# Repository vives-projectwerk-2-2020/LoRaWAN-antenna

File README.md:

# The LoRaWAN-antenna board

This is the explanation of how the antenna PCB board came. And how you can make one yourself.
This PCB described here must then be connected to the main PCB. Below you can see what it looks like.

This Antenna on the board is based on [this](http://www.ti.com/lit/an/swra228c/swra228c.pdf) design.

## Explanation of the Antenna PCB board

Below you see the antenna board. The PCB antenna on this board is suitable for a frequency around 868MHz.

The antenna will work most efficiently if it is resonant. When it is resonant, the maximum power will be radiated by the antenna. If an antenna is not resonant, some of the power will not be transmitted. The power is reflected back to the transmitter (in our case the RF96 module).

Because of the reflection you have a RF power loss and you could damage the RF96 module and also reduce your transmission range.

You can solve this by doing 2 things:

* Adjust the length of the antenna and,
* add a matching network.

This is discussed below here.

### Adjust length

You can adjust the length here, by scratching away some copper at the end of the antenna. The total length of the last piece of the antenna is 1,25 cm (measured from the outer corner). See the image below for clarification.

By adjusting the length of the antenna, the antenna is now al more suitable for 868MHz.

### Matching network

By adding a matching network now, we can improve the impedance of the antenna more.

The network for adjusting the impedance is a PI network. Below you can see the schematic of the network. The left side of the math unit is connected to the RF96 (the antenna output = pin 9). The right side of the unit is connected to the antenna.

You can observe the matching network below. This consists of 2 capacitors and 1 coil. The values of the capacitors are 2,2pF. The value of the coil is 12nH.

Due to mismatches in impedance, some of the signal is reflected. The ratio of the input to the reflected signal is called the Voltage Standing Wave Ratio (VSWR). This ratio can also be measured in dB, and expressed as Return Loss.

Below you can see that the VSWR at 868MHz is 1.112. This mean that you're return lose is 25.510dB. This is very good, because now less than 1% of the power goes back to the module. This means that more than 99% of the power is used for the communication.

The dimensions of the PCB are also very important. If the dimensions are different from here, you must again determine the length and the matching network.

### RF96

The RF96 module is a module suitable for ultra-long range spread spectrum communications. This module has a 20 dBm power amplifier. This means that you have an output power of 100mW. Because the impedance is now correct, all power will also be radiated effectively.

Below you see the RF95 module. All pins are brought out through the pins. Except the pin that goes to the antenna.
This PCB is then clicked on the main PCB.

### schematic and print in Eagle

Here you can see the schematic drawn in Eagle. At the top you see the pins, these are then connected to the main PCB. below that you see the RF96 chip.
In the middle you see the matching network, which ensures a correct impedance.
The square block on the right is the symbol for your antenna. It is a symbol whose foodprint is the shape of the antenna.

Below you can see what the PCB looks like in eagle.

### tests that happened

You can view the tests that happened in the folder "testing".

## Make it yourself

### Develop the PCB

First you need to develop the PCB. You can do this by sending a zip to a manufacturer. Like for example with this manufacturer([JLCPCB](https://jlcpcb.com/)).
The ZIP file is located here in the root and is called 'LoRaWAN_antenna.zip'. You can download and upload this on the manufacturer's website. If you want to make changes to the PCB you can edit it in the folder 'PCB-antenna-eagle'.

### Order the components

Then you have to order the components. These are the components:

* [coil (12nH)](https://be.farnell.com/te-connectivity/36502a12njtdg/inductor-12n-5-0805-case/dp/1265504?st=)
* [capacitors (2.2pF)](https://be.farnell.com/vishay/vj0805a2r2bxapw1bc/cap-2-2pf-50v-c0g-np0-0805/dp/2896503?st=)
* [RF96 module](https://www.digikey.be/product-detail/en/seeed-technology-co.,-ltd/109990166/1597-1488-ND/7033232?utm_adgroup=RF%20Transceiver%20Modules&utm_source=google&utm_medium=cpc&utm_campaign=Shopping_Product_RF%2FIF%20and%20RFID&utm_term=&productid=7033232&gclid=CjwKCAjwqpP2BRBTEiwAfpiD-0hUd9VhSiN13Y9OhOWbJ38YxABk0f2ujbqdI1xJR1xy0auqC77hRBoC65kQAvD_BwE)
* [male pins](https://be.farnell.com/harwin/m20-9990846/connector-header-tht-2-54mm-8way/dp/1022257)

for 1 PCB you need 2 capacitors, 1 coil, 1 RF95 module and 15 male pins.

### Solder everything together

If you then have your PCB and components, you can start soldering.
You should not scratch the antenna anymore, I have already adjusted this in the last version.
For soldering it is best to start with the RF96 module and then the capacitors and the coil.
Then solder the pins on the last.

## Placing the installation

If you have connected all the boards(main + solar + antenna), you can place this where you want.
There are some things to keep in mind:

* Place the installation in a place where connections can be made to a gateway. On [this](https://www.thethingsnetwork.org/map) map you can see where there is a gateway. If you want a map where you can see the range, it is best to use [this map](https://ttnmapper.org/).

* Place the installation as high as possible. The higher, the fewer obstacles in the way and the greater the chance of connecting to a gateway.

* Do not place the antenna under the solar panels or next to the solar panels. Because this will ensure that a lot of your range is gone.

* The box you use should not be made of metal or a substance containing metal. [This](http://www.farnell.com/datasheets/2360495.pdf?_ga=2.70667346.396449874.1589637555-1552518953.1588835899&_gac=1.258009592.1589039175.CjwKCAjwqdn1BRBREiwAEbZcR9CB4ETaMQ7lKFncoM-7RMHN5OMiYtTP339AnwNVqZjWkSkDVfl0shoCSGMQAvD_BwE) box is ideal. The material from which the box is made is Polycarbonate. This does not contain metal.

* The box with should be placed freely, not against a wall. Also make sure you are at a certain height.

* Make sure the box is not completely closed. It is best to make 1 or 2 small holes at the bottom so that moisture can escape if condensation forms.

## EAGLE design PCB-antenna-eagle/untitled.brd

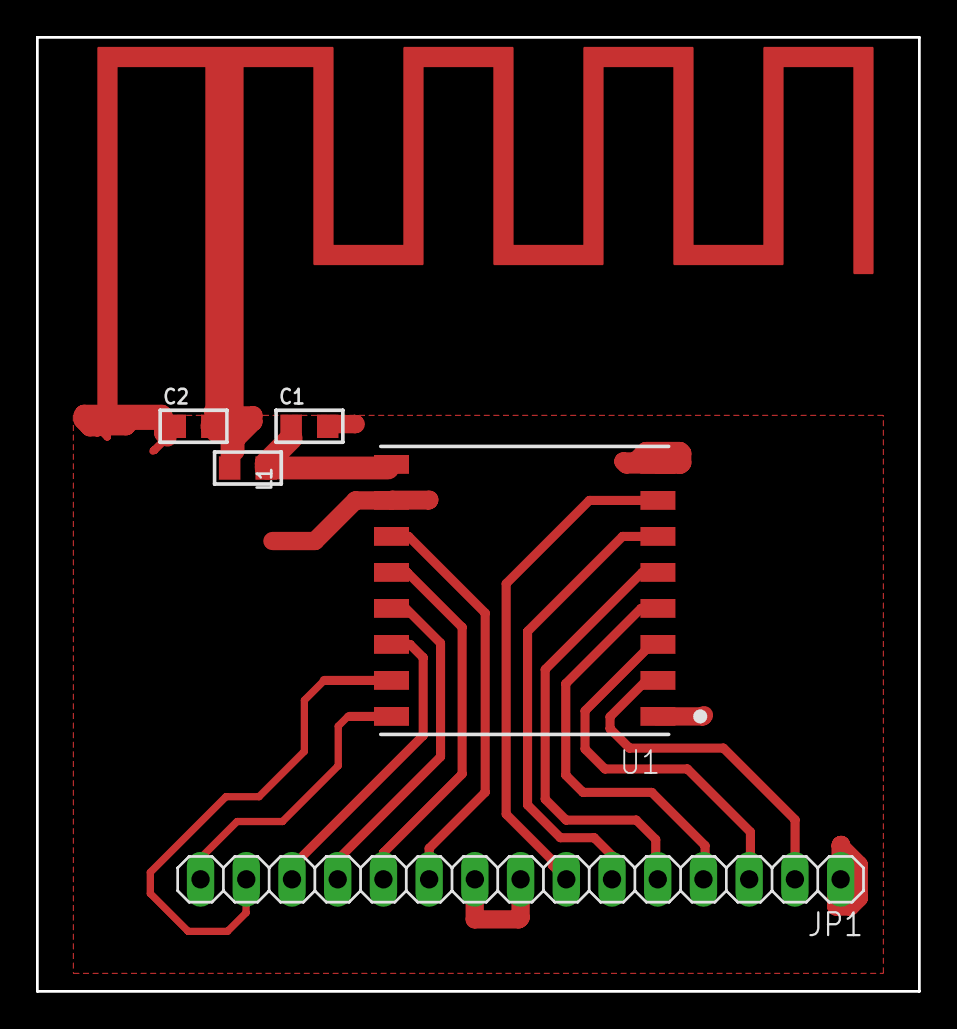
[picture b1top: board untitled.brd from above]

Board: 2 copper layers, 49.0 x 53.0 mm, 6 parts (0 on the bottom side), 15 nets.

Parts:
C1, C2: C0805
JP1: 1X15
L1: L_0805; L0805
U1: RFM95W-868S2; XCVR_RFM95W-868S2
U$1: 868

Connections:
GND: C1.2, C2.1, JP1.1, JP1.8, JP1.9, U1.1, U1.8, U1.10, U$1.P$1
unnamed: C2.2, L1.2, U$1.P$2
unnamed: C1.1, L1.1, U1.9
unnamed: JP1.2, U1.2
unnamed: JP1.3, U1.3
unnamed: JP1.4, U1.4
unnamed: JP1.5, U1.5
unnamed: JP1.6, U1.6
unnamed: JP1.7, U1.7
unnamed: JP1.10, U1.11
unnamed: JP1.11, U1.12
unnamed: JP1.12, U1.13
unnamed: JP1.13, U1.14
unnamed: JP1.14, U1.15
unnamed: JP1.15, U1.16

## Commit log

2020-02-18 add photo of the bests antennas
2020-02-18 research update
2020-02-18 research update 2
2020-02-18 research update 3
2020-02-18 research update 4
2020-02-18 add doc+ research
2020-02-18 PCB-antenna is not optimal
2020-02-19 chanches to word
2020-02-19 Research part 6
2020-02-27 gasket antenna will be to big
2020-02-27 update from research
2020-02-27 found the antenna
2020-02-27 verdere stappen
2020-03-01 design PCB antenna
2020-03-03 add inkcape design from antenna
2020-03-03 add picture of antenna_drawing
2020-03-08 draw the PCB for a part
2020-03-10 groundplane
2020-03-10 add antenna
2020-03-10 full_print
2020-03-10 try to print on mika -- failed
2020-03-11 add pdf for etsing
2020-03-11 add zip for making pcb
2020-03-15 add partlist for prototype
2020-03-15 add some documentation
2020-03-29 solder and test antenna
2020-04-06 solder the board with module
2020-04-11 connect the arduino and RF95 for testing
2020-04-11 level converters
2020-04-14 try to test program
2020-04-21 test the board with the board of Niels - Succcesful
2020-04-21 test the range a bit
2020-04-27 test with better antenna on the gateway
2020-05-04 change PCB antenna to the best dimensions
2020-05-08 different between the two antenna's
2020-05-09 remove some typos
2020-05-09 add matching explanation
2020-05-09 change image
2020-05-09 change name
2020-05-09 add somme explanation about VSWR
2020-05-09 RF95
2020-05-09 add eagle stuff
2020-05-09 add image
2020-05-09 remove some old stuff
2020-05-09 add source and intro
2020-05-09 remove typo
2020-05-09 change
2020-05-09 add upercase letters
2020-05-09 add schematic
2020-05-09 replace PCB
2020-05-09 add components
2020-05-09 add some intro on RF95
2020-05-09 remove some stuff
2020-05-09 replace stuff
2020-05-09 change name folder
2020-05-09 add section testing
2020-05-09 change testing readme
2020-05-09 change documentation about testing
2020-05-09 add some subtitles
2020-05-09 change titles
2020-05-11 add some old stuff
2020-05-11 read and adjust some text
2020-05-11 change text
2020-05-11 retyp some text
2020-05-16 add instalation instrucions
2020-05-20 change RF95 to RF96
2020-05-21 change farady to henry

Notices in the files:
parts and their libraries:
rc-master-smd: Copyright (C) 2007, Bob Starr
